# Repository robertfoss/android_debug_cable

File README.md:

# Android Debug Cable

## Connector

    ####|###|==|==>
    3.3V GND RX  TX

## Changelog

v0.7:
 - Fix VBUS being unconnected
 - Shrink connector holes

v0.6:
- Fix C1 to be actually decoupling

v0.5:
- Switch to throughole 3.5mm connector

v0.4:
- Cost reductions:
  * Switch to male 3.5mm connector
  * Switch from CP2103 to CP2102N
  * Switch to cheaper 1.8v reg
  * Switch to only one cap value
  * Smaller PCB

v0.3:

- Changed 3.5mm connector mechanical hole to have no copper

v0.2:

- Moved logo position
- Moved a via to make space for a more centered logo
- Moved RX/TX/GND/V3.3 text
- Updated verion text
- Increased outline corner radius
- Increased board width with 0.02mm to 12.2mm
- Switched RX/TX pins on 3.5mm connector

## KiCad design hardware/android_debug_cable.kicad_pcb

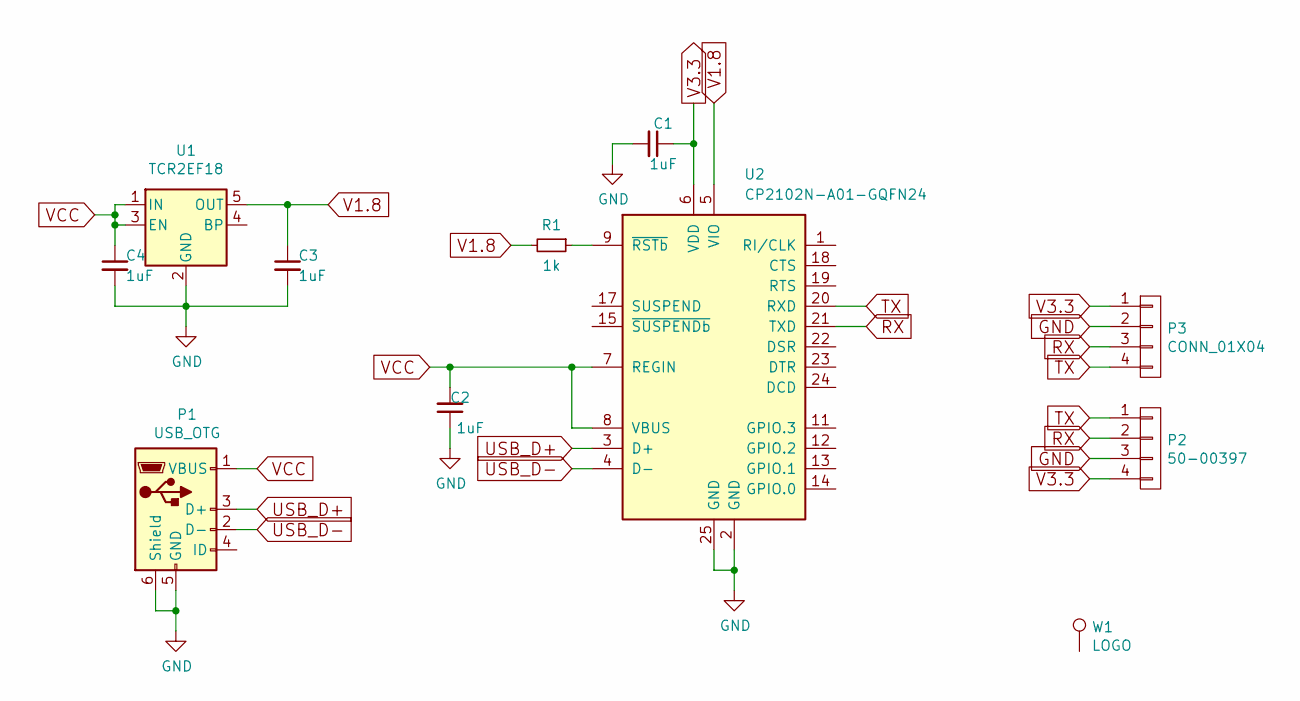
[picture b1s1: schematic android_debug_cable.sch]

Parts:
C1: 1uF
C2, C3, C4: 1uF; C_0402
P1: USB_OTG; USB_Micro-B
P2: 50-00397
P3: CONN_01X04; CONN_2.54mm_1x4_no-outline
R1: 1k; R_0402
U1: TCR2EF18; SOT-23-5
U2: CP2102N-A01-GQFN24; QFN-24-1EP_4x4mm_Pitch0.5mm
W1: LOGO; copperhead_logo

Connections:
GND: C1.2, C2.1, C3.2, C4.2, P1.5 (GND), P1.6 (Shield), P2.3, P3.2, U1.2 (GND), U2.2 (GND), U2.25 (GND)
unnamed: R1.1, U2.9 (~RSTb)
RX: P2.2, P3.3, U2.21 (TXD)
TX: P2.1, P3.4, U2.20 (RXD)
USB_D+: P1.3 (D+), U2.3 (D+)
USB_D-: P1.2 (D-), U2.4 (D-)
V1.8: C3.1, R1.2, U1.5 (OUT), U2.5 (VIO)
V3.3: C1.1, P2.4, P3.1, U2.6 (VDD)
VCC: C2.2, C4.1, P1.1 (VBUS), U1.1 (IN), U1.3 (EN), U2.7 (REGIN), U2.8 (VBUS)

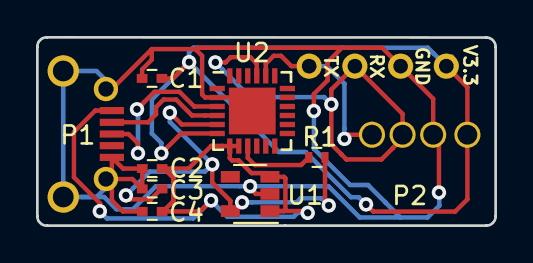
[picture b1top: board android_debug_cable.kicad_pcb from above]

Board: 2 copper layers, 25.5 x 10.5 mm, 11 parts (1 on the bottom side), 9 nets.

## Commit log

2016-08-14 v0.1 with copperhead branding
2016-08-14 Added gerbers for v0.1_copperhead
2016-08-14 Added raytrace of v0.1_copperhead
2016-08-19 Added v0.1 copperhead renders
2016-08-19 Images moved to media branch.
2016-08-31 Add v0.2
2016-08-31 Add v0.2_copperhead
2016-10-03 Updated 3.5mm connector footprint
2016-10-03 Switch images
2016-10-03 Added rev0.3 front
2017-01-12 Remove Copperhead branding, bump to v0.3
2017-06-18 Add TCR2EF18, CP2102N and 50-00397 datasheets
2017-06-19 Add Seeed compatible bom
2017-06-20 Add first version of v0.4
2017-06-20 Add connector info
2017-06-20 Updated changelog
2017-06-20 Switch to v0.4 render
2017-06-20 Change direction of connector info
2017-06-20 Improve changelog
2017-06-20 Changed 3.5mm connector pinout
2017-06-20 Add render of v0.4
2017-06-20 Fixed CP2102N power sourcing
2017-06-21 Edit MicoUSB footprint
2017-06-21 Move vias away from logo
2017-06-27 Add 54-00035 connector files
2017-06-27 Add v0.5 using throughole 3.5mm connector
2017-06-28 Add v0.5_front raytrace
2017-07-01 Added black colored insulator to 54-00035 step
2017-07-01 Update render with black insulator on 3.5mm connector
2017-07-01 Move logo/version number around
2017-07-01 v0.6
2017-07-01 Updated README.md image
2017-07-07 Add altconn version of v0.6
2017-07-16 Added FIXMEs for v0.7
2017-07-19 54-00035: shrunk holes
2017-07-19 Fixed VBUS not being connected, shrunk connector through holes
2017-07-20 v0.7
